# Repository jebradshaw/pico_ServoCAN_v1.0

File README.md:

# pico_ServoCAN_v1.0
RasPi Pico RP2040 Sevo CAN Microcontroller Board

This RasPi Pico RP2040 microcontroller board contains an MCP2515 SPI CAN bus transceiver and driver electronics, GPIO accessible ports, an I2C port with STEMMA and JST-XH connectors, two power FET driver ports, an on board 5 volt 2 amp DC-DC switching power supply, a TTL level serial UART, and jumper options.

Note that on version 1.0, the MCP2515 18-pin DIP package needs pin 17 (!RESET) tied high, usuaally through a solder jumper from pin 17 to pin 18 (Vcc) on the underside of the PCB.
  Also pin 8 (STBY) of the MCP2561 CAN transceiver should be tied LOW to ground through an external wire jumper.

Also note that the board was originally designed using an OKI 78SR Series 5V 1.5A regulator (U4), which are now very difficult to come by.  So the part has been replaced with a VR20S05 5 volt 2 amp regulator which comes in a slightly larger, sealed, package (available from Digikey - https://www.xppower.com/portals/0/pdfs/SF_VR20.pdf).  To get this regulator to fit on the board, C6 (a .1uF capacitor) should not be soldered in place.

KiCAD 3D render of PCB

Schematic (PDF format) - [pico_Kingfisher_2023.pdf](https://github.com/jebradshaw/pico_ServoCAN_v1.0/files/12242137/pico_Kingfisher_2023.pdf)

  If using Adafruits Circuit Python (which I like for the RP2040), copy the lib folder contents to the pico drive under .lib to include the CAN libraries for the CAN bus controller.  An example program to test the CAN transmit and receive functionality is also included.

  Also added is an Arduino (which I also really like) sketch for the CAN interface and servo outs running on both cores overclocked to 250MHz (Core Temp ~ 31 deg C).

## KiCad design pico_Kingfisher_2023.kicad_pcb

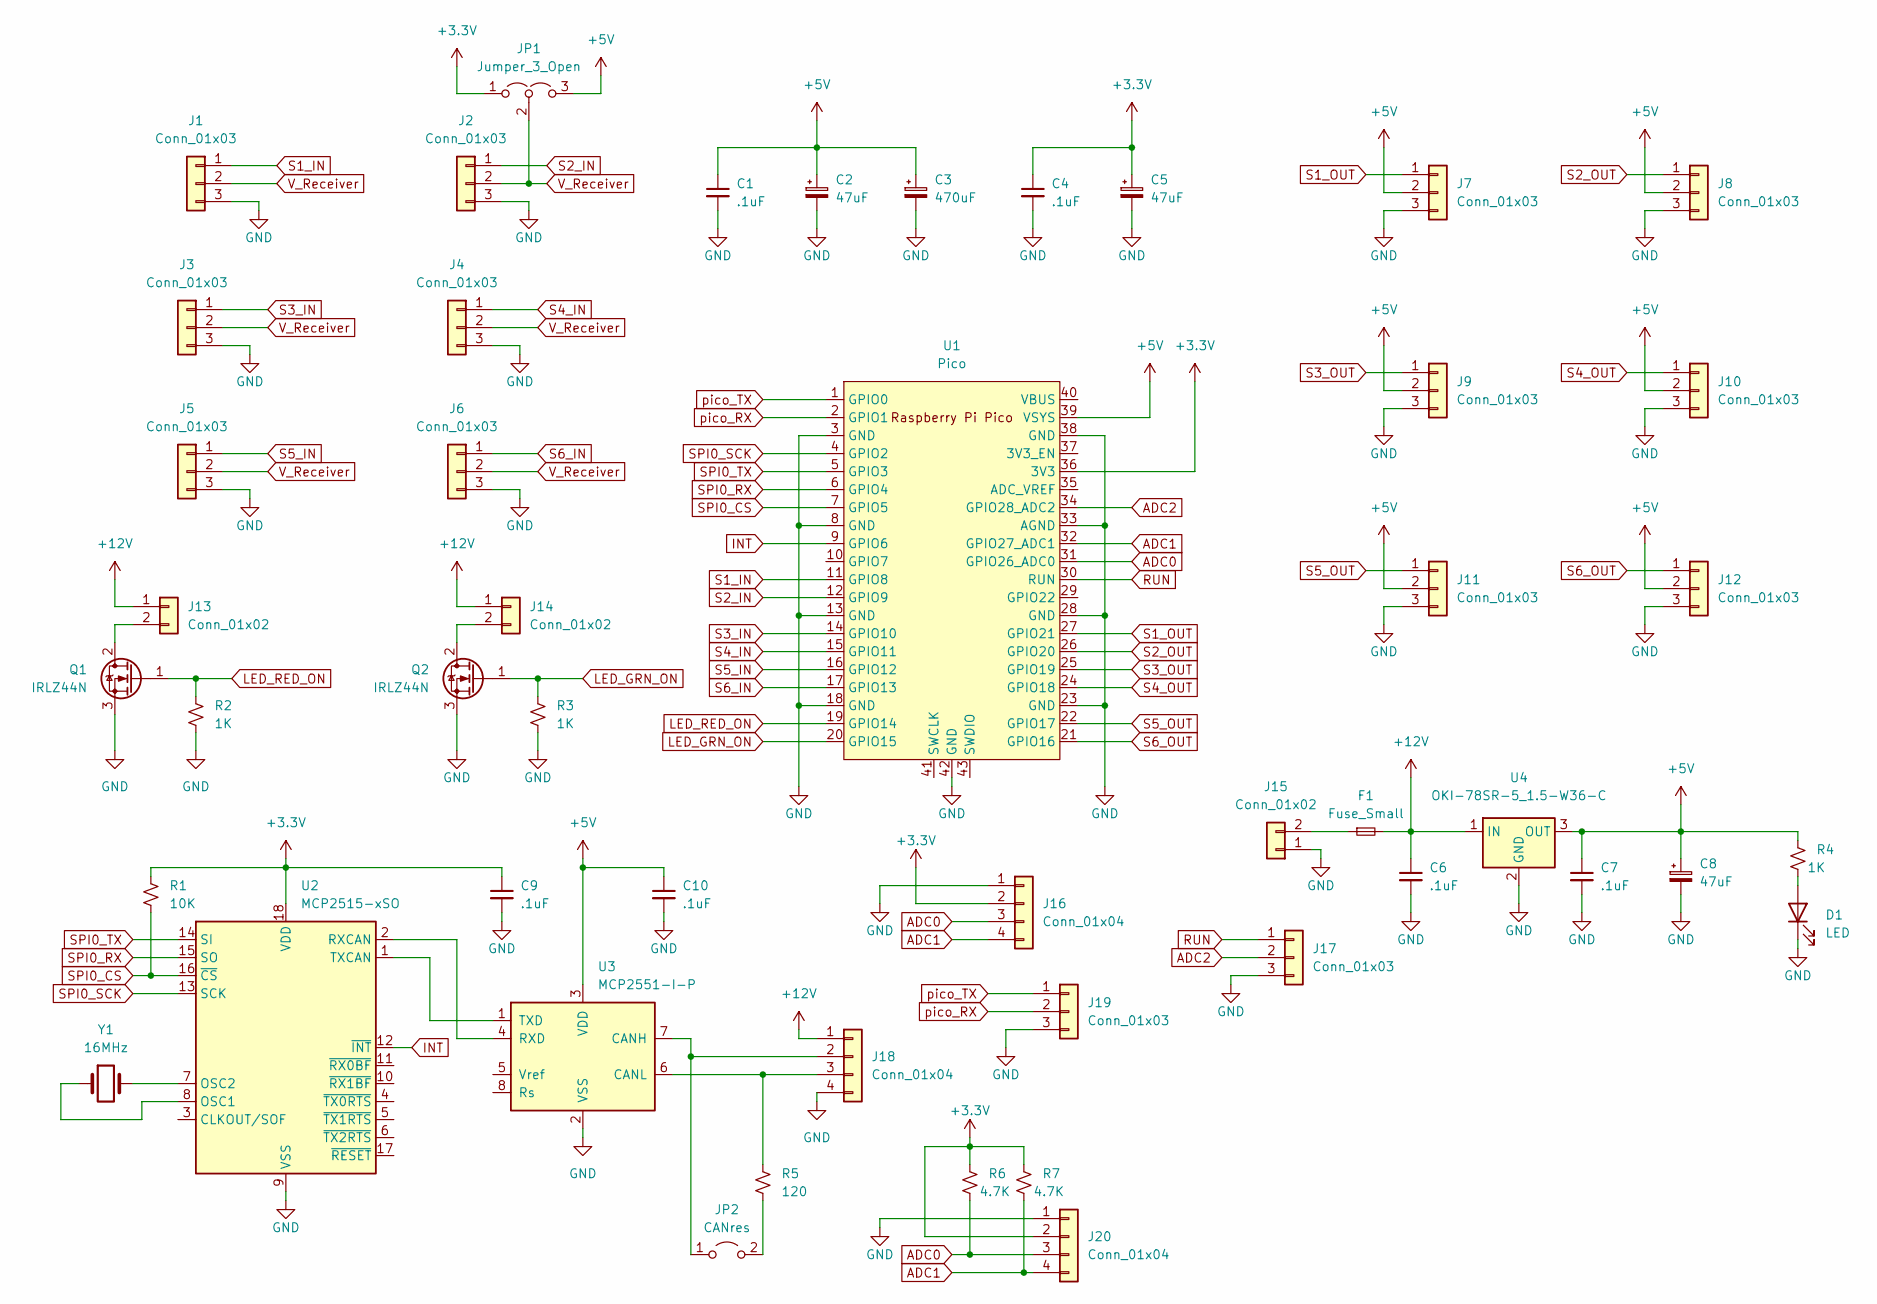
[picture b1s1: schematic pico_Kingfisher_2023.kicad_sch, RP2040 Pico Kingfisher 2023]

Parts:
C1, C4, C6, C7, C9, C10: .1uF; C_Disc_D5.0mm_W2.5mm_P2.50mm
C2, C5, C8: 47uF; CP_Radial_D5.0mm_P2.50mm
C3: 470uF; CP_Radial_D5.0mm_P2.50mm
D1: LED; LED_D3.0mm
F1: Fuse_Small; Fuse_Littelfuse_395Series
J1, J2, J3, J4, J5, J6, J7, J8, J9, J10, J11, J12, J19: Conn_01x03; PinHeader_1x03_P2.54mm_Vertical
J13, J14, J15: Conn_01x02; JST_XH_B2B-XH-A_1x02_P2.50mm_Vertical
J16, J18: Conn_01x04; JST_XH_B4B-XH-A_1x04_P2.50mm_Vertical
J17: Conn_01x03; JST_XH_B3B-XH-A_1x03_P2.50mm_Vertical
J20: Conn_01x04; JST_SH_SM04B-SRSS-TB_1x04-1MP_P1.00mm_Horizontal
JP1: Jumper_3_Open; PinHeader_1x03_P2.54mm_Vertical
JP2: CANres; PinHeader_1x02_P2.54mm_Vertical
Q1, Q2: IRLZ44N; TO-220-3_Horizontal_TabDown
R1: 10K; R_Axial_DIN0204_L3.6mm_D1.6mm_P7.62mm_Horizontal
R2, R3, R4: 1K; R_Axial_DIN0204_L3.6mm_D1.6mm_P7.62mm_Horizontal
R5: 120; R_Axial_DIN0204_L3.6mm_D1.6mm_P7.62mm_Horizontal
R6, R7: 4.7K; R_Axial_DIN0204_L3.6mm_D1.6mm_P7.62mm_Horizontal
U1: Pico; RPi_Pico_SMD_TH
U2: MCP2515-xSO; DIP-18_W7.62mm
U3: MCP2551-I-P; DIP-8_W7.62mm
U4: OKI-78SR-5_1.5-W36-C; Converter_DCDC_Murata_OKI-78SR_Vertical
Y1: 16MHz; Crystal_HC49-4H_Vertical

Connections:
+3.3V: C4.1, C5.1, C9.1, J16.2, J20.2, JP1.1 (A), R1.1, R6.1, R7.1, U1.36 (3V3), U2.18 (VDD)
+5V: C1.1, C2.1, C3.1, C7.1, C8.1, C10.1, J7.2, J8.2, J9.2, J10.2, J11.2, J12.2, JP1.3 (B), R4.1, U1.39 (VSYS), U3.3 (VDD), U4.3 (OUT)
+12V: C6.1, F1.2, J13.1, J14.1, J18.1, U4.1 (IN)
ADC0: J16.3, J20.3, R6.2, U1.31 (GPIO26_ADC0)
ADC1: J16.4, J20.4, R7.2, U1.32 (GPIO27_ADC1)
ADC2: J17.2, U1.34 (GPIO28_ADC2)
GND: C1.2, C2.2, C3.2, C4.2, C5.2, C6.2, C7.2, C8.2, C9.2, C10.2, D1.1 (K), J1.3, J2.3, J3.3, J4.3, J5.3, J6.3, J7.3, J8.3, J9.3, J10.3, J11.3, J12.3, J15.1, J16.1, J17.3, J18.4, J19.3, J20.1, Q1.3 (S), Q2.3 (S), R2.2, R3.2, U1.3 (GND), U1.8 (GND), U1.13 (GND), U1.18 (GND), U1.23 (GND), U1.28 (GND), U1.33 (AGND), U1.38 (GND), U1.42 (GND), U2.9 (VSS), U3.2 (VSS), U4.2 (GND)
INT: U1.9 (GPIO6), U2.12 (~INT)
LED_GRN_ON: Q2.1 (G), R3.1, U1.20 (GPIO15)
LED_RED_ON: Q1.1 (G), R2.1, U1.19 (GPIO14)
unnamed: J13.2, Q1.2 (D)
unnamed: J14.2, Q2.2 (D)
unnamed: F1.1, J15.2
unnamed: J18.2, JP2.1 (A), U3.7 (CANH)
unnamed: J18.3, R5.1, U3.6 (CANL)
unnamed: JP2.2 (B), R5.2
unnamed: D1.2 (A), R4.2
unnamed: U2.1 (TXCAN), U3.1 (TXD)
unnamed: U2.2 (RXCAN), U3.4 (RXD)
unnamed: U2.7 (OSC2), Y1.2
unnamed: U2.8 (OSC1), Y1.1
RUN: J17.1, U1.30 (RUN)
S1_IN: J1.1, U1.11 (GPIO8)
S1_OUT: J7.1, U1.27 (GPIO21)
S2_IN: J2.1, U1.12 (GPIO9)
S2_OUT: J8.1, U1.26 (GPIO20)
S3_IN: J3.1, U1.14 (GPIO10)
S3_OUT: J9.1, U1.25 (GPIO19)
S4_IN: J4.1, U1.15 (GPIO11)
S4_OUT: J10.1, U1.24 (GPIO18)
S5_IN: J5.1, U1.16 (GPIO12)
S5_OUT: J11.1, U1.22 (GPIO17)
S6_IN: J6.1, U1.17 (GPIO13)
S6_OUT: J12.1, U1.21 (GPIO16)
SPI0_CS: R1.2, U1.7 (GPIO5), U2.16 (~CS)
SPI0_RX: U1.6 (GPIO4), U2.15 (SO)
SPI0_SCK: U1.4 (GPIO2), U2.13 (SCK)
SPI0_TX: U1.5 (GPIO3), U2.14 (SI)
V_Receiver: J1.2, J2.2, J3.2, J4.2, J5.2, J6.2, JP1.2 (C)
pico_RX: J19.2, U1.2 (GPIO1)
pico_TX: J19.1, U1.1 (GPIO0)

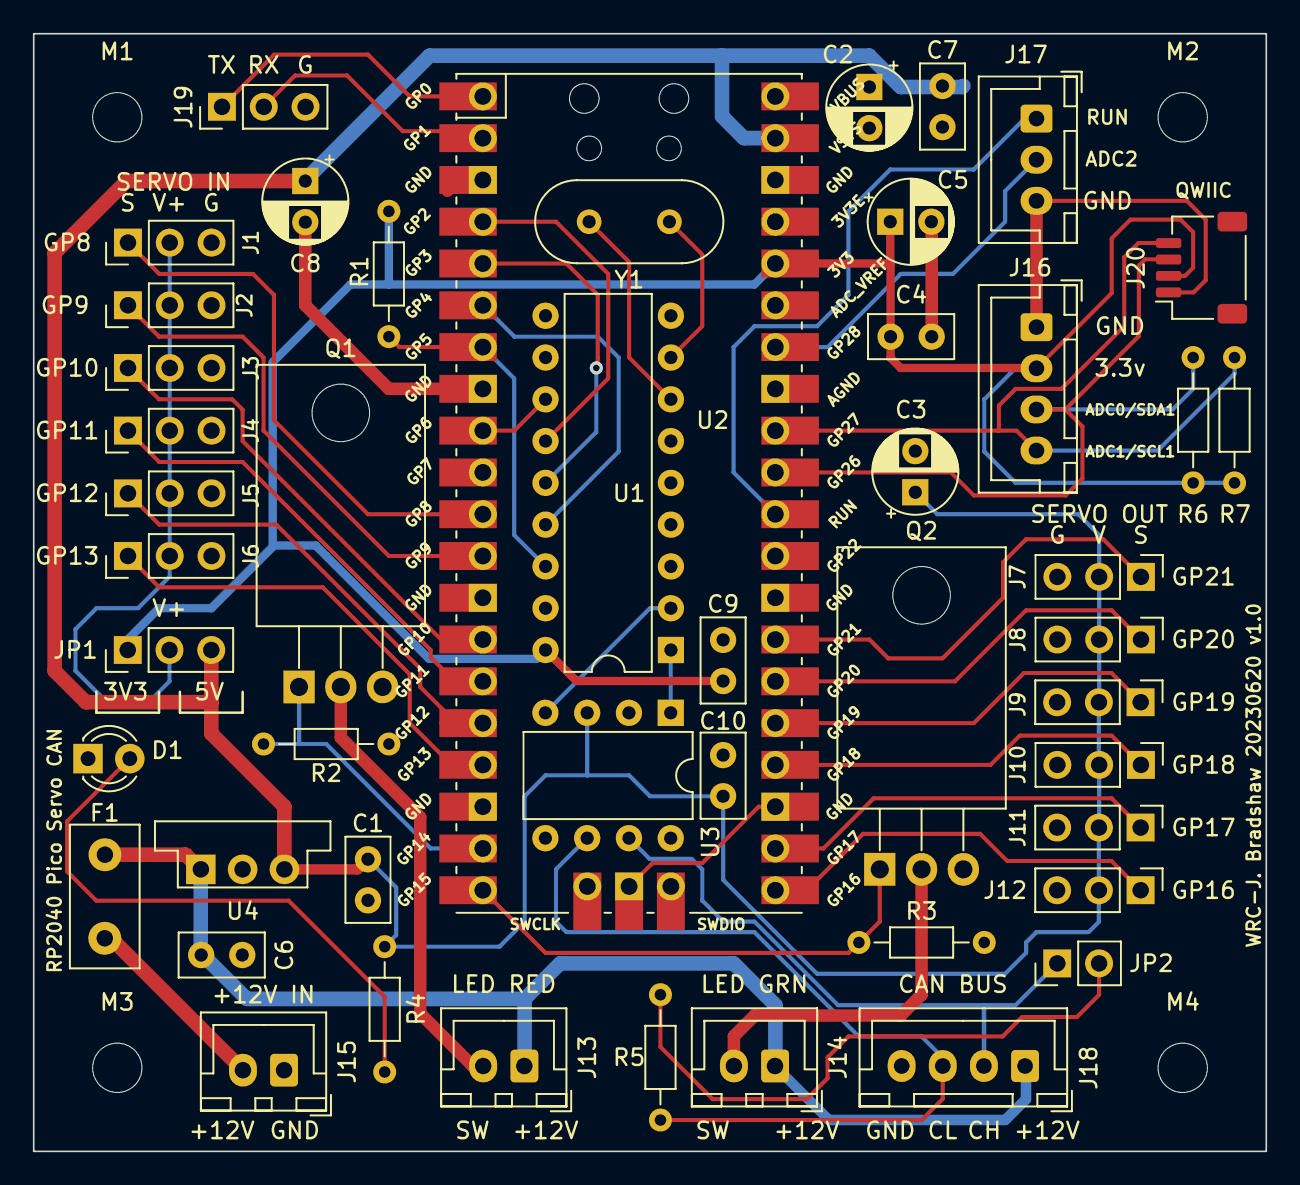
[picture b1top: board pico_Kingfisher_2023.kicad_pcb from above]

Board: 2 copper layers, 74.9 x 67.9 mm, 52 parts (0 on the bottom side), 41 nets.

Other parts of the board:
M1, M2, M3, M4: MountingHole_3mm

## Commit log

2023-10-27 Arduino Pico Template Sketch and uf2 file
    250MHz overclock clock (core ~31 deg C)
    Tests CAN, LED, servo outs
